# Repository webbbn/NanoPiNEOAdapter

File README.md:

# NanoPiNEOAdapter
An adapter board to mount a FriendlyARM NanOPI NEO on a standard stack of 36x36 flight controller boards

Version 1.0 boards can be ordered here: https://oshpark.com/shared_projects/PryW8AIs

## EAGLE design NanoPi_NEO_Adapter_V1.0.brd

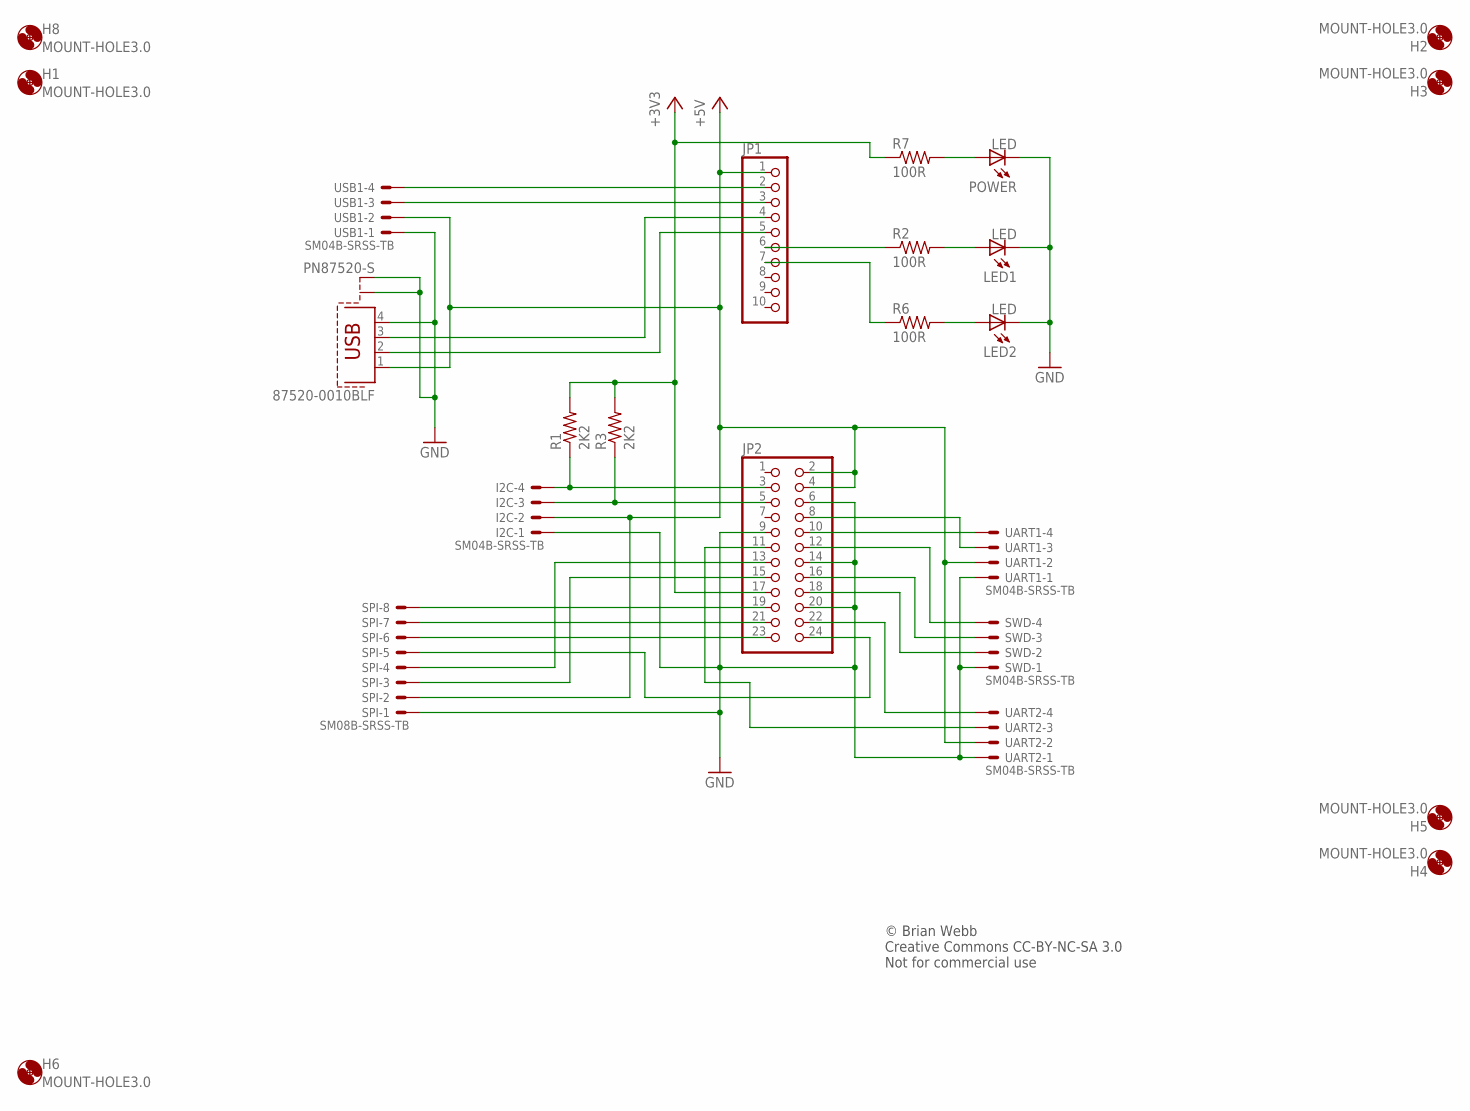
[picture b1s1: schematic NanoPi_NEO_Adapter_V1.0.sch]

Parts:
87520-0010BLF: PN87520-S
H1, H2, H3, H4, H5, H6, H8: MOUNT-HOLE3.0; 3,0
I2C: SM04B-SRSS-TB
JP1: PINHD-1X10; 1X10
JP2: PINHD-2X12; 2X12
LED1, LED2: LED; LED0402
POWER: LED; LED0402
R1, R3: 2K2; R0402; PARTNO ERJ-2GEJ222X
R2, R6, R7: 100R; R0402; PARTNO ERJ-2GEJ222X
SPI: SM08B-SRSS-TB
SWD: SM04B-SRSS-TB
UART1, UART2: SM04B-SRSS-TB
USB1: SM04B-SRSS-TB

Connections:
+3V3: JP2.17, R1.2, R3.2, R7.1
+5V: 87520-0010BLF.1, I2C.2, JP1.1, JP2.2, JP2.4, SPI.2, UART1.2, UART2.2, USB1.2
GND: 87520-0010BLF.4, 87520-0010BLF.S1, 87520-0010BLF.S2, I2C.1, JP2.6, JP2.9, JP2.14, JP2.20, LED1.C, LED2.C, POWER.C, SPI.1, SWD.1, UART1.1, UART2.1, USB1.1
unnamed: JP1.2, USB1.4
unnamed: JP1.3, USB1.3
unnamed: JP2.10, UART1.4
unnamed: JP2.8, UART1.3
unnamed: 87520-0010BLF.3, JP1.4
unnamed: 87520-0010BLF.2, JP1.5
unnamed: JP2.19, SPI.8
unnamed: JP2.22, UART2.4
unnamed: JP2.18, SWD.2
unnamed: I2C.4, JP2.3, R1.1
unnamed: I2C.3, JP2.5, R3.1
unnamed: JP2.21, SPI.7
unnamed: JP2.23, SPI.6
unnamed: JP2.24, SPI.5
unnamed: JP2.13, SPI.4
unnamed: JP2.15, SPI.3
unnamed: LED2.A, R6.2
unnamed: LED1.A, R2.2
unnamed: POWER.A, R7.2
unnamed: JP2.11, UART2.3
unnamed: JP1.6, R2.1
unnamed: JP1.7, R6.1
unnamed: JP2.16, SWD.3
unnamed: JP2.12, SWD.4

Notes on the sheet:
© Brian Webb Creative Commons CC-BY-NC-SA 3.0 Not for commercial use

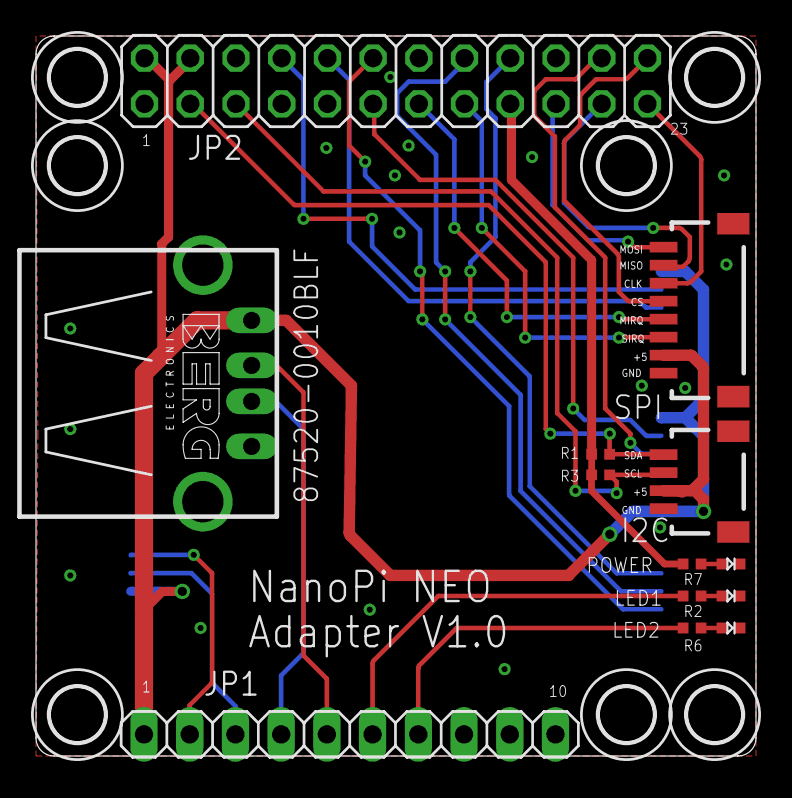
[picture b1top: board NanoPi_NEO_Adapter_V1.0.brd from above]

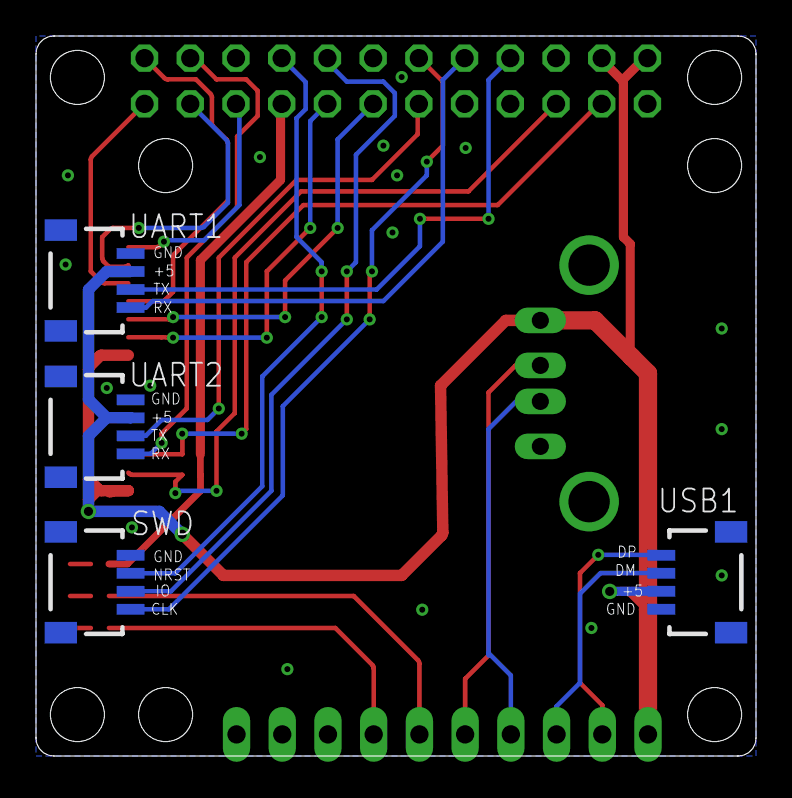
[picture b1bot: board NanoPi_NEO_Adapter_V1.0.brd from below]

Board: 2 copper layers, 40.0 x 40.0 mm, 24 parts (4 on the bottom side), 27 nets.

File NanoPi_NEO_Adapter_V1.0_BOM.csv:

Part,Digi-Key Part Number,Manufacturer,Manufacturer Part Number,Customer Reference,Quantity 1,Quantity 2,Quantity 3,Mfg Std Lead Time,Description,Comments,RoHS Status,Lead Free Status,REACH Status
USB,609-1045-ND,AMPHENOL FCI,87520-0010BLF,,1,0,0,17 Weeks,CONN RCPT USB TYPE A R/A PCB,,RoHS Compliant,Lead free,Not Available
JP1,S7008-ND,SULLINS CONNECTOR SOLUTIONS,PPTC101LFBN-RC,,1,0,0,3 Weeks,"CONN HEADER FEMALE 10POS.1"" TIN",,RoHS Compliant,Lead free,Unaffected Dec-2015
JP2,S7115-ND,SULLINS CONNECTOR SOLUTIONS,PPPC122LFBN-RC,,1,0,0,3 Weeks,"CONN HEADER FMAL 24PS.1"" DL GOLD",,RoHS Compliant,Lead free,Unaffected Dec-2015
USB1 UART1 SWD UART2,455-1804-1-ND,JST SALES AMERICA INC (VA),SM04B-SRSS-TB(LF)(SN),,4,0,0,14 Weeks,CONN HEADER SH 4POS SIDE 1MM TIN,Alternate Packaging Exists,RoHS Compliant,Lead free,Not Available
SPI,455-1808-1-ND,JST SALES AMERICA INC (VA),SM08B-SRSS-TB(LF)(SN),,1,0,0,14 Weeks,CONN HEADER SH 8POS SIDE 1MM TIN,Alternate Packaging Exists,RoHS Compliant,Lead free,Not Available
R1 R3,P2.2KJCT-ND,PANASONIC ELECTRONIC COMPONENTS (VA),ERJ-2GEJ222X,,2,0,0,6 Weeks,RES SMD 2.2K OHM 5% 1/10W 0402,Alternate Packaging Exists,RoHS Compliant,Lead free,Unaffected Jun-2015
R2 R6 R7,P100JCT-ND,PANASONIC ELECTRONIC COMPONENTS (VA),ERJ-2GEJ101X,,3,0,0,6 Weeks,RES SMD 100 OHM 5% 1/10W 0402,Alternate Packaging Exists,RoHS Compliant,Lead free,Unaffected Jun-2015
POWER,846-1191-1-ND,ROHM SEMICONDUCTOR(VA),SML-P12M2TT86R,,1,0,0,10 Weeks,LED HB 576NM YWGN TRANSP 1006,Alternate Packaging Exists,RoHS Compliant,Lead free,Unaffected Jun-2015
LED1,846-1168-1-ND,ROHM SEMICONDUCTOR(VA),SML-P12VTT86R,,1,0,0,10 Weeks,LED RED CLEAR 0402 SMD,Alternate Packaging Exists,RoHS Compliant,Lead free,Unaffected Jun-2015
LED2,846-1204-1-ND,ROHM SEMICONDUCTOR(VA),SML-P12YTT86R,,1,0,0,8 Weeks,LED YELLOW CLEAR 0402 SMD,,RoHS Compliant,Lead free,Not Available

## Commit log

2016-08-06 Adds initial V1.0 shematic and board.
2016-08-06 Minor updates to complete V1.0 and adds board PDF files.
2016-08-06 Updated license
2016-08-06 Updated the board PDF files with a new style.
2016-08-10 Added V1.0 BOM
